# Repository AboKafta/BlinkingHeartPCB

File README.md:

# BlinkingHeartPCB
## Initial Prototype (Summer 2025)

A simple prototype was first made during the summer of 2025 as a gift for my girlfriend. After looking up some tutorials and many hours, I got a simple prototype. I tumbled into some problems such as putting footprints, design errors, and generating a BoM. After using JLCPCB, this is how it was supposed to look. However, after seeing how much it would cost and if it would even work, I didn't continue to manufacture it. A lot of steps were missed in the process (correct factory specifications, wrong gerber file, etc…) and contained a variety of through-hole and SMD parts.

## Second Iteration (2026)

The goal is to make around the same but this time using a 555 timer to make it blink, use only through-hole components to make it easily solderable, and make it smaller and more appeasing. 

# Prototype

Using a guide from https://www.instructables.com/Flashing-LED-using-555-Timer/, a prototype on TinkerCAD was built. Modifications were:

- potentiometer which acts as a rheostat to change blinking speed instead of 1 set blinking speed
- 13 additional LEDs with 100ohm corresponding resistor
- 9V battery to 3V battery cell for convenience, with switch added

A prototype was made in TinkerCAD to check if everything works well before going on to making a schematic: https://www.tinkercad.com/things/8CvfxhTKkNE-blinking-led

# Schematic

Helpful KiCad tutorial: https://www.youtube.com/watch v=HAlTS3Bm8C4&list=PLUOaI24LpvQPls1Ru_qECJrENwzD7XImd&index=3

In KiCad, the base schematic was transformed from:

To:

Notes:

- Resistor values on LEDs can be made higher to change duration of cell battery but LEDs won’t be as bright.
- If LED colors wants to be swapped, make sure the forward voltage is around 2V. Anything above 3V will ensure dim lights and low battery run time.
- The battery cell itself was bought off amazon rather than Digikey.
- 50ohm resistors to LEDs were kept to keep the current at a safe level and not rely on the cell battery’s internal resistance which is prone to spikes.
- Make sure the chosen 555 timer takes 3V, some take 4.5V and above only.

Parts Selected:

All items were found off Digikey and contain all the necessary symbols and footprints except the yellow LEDs, but that can be assigned to a basic 5mm LED footprint found on KiCad:

- Switch: https://www.digikey.com/en/products/detail/e-switch/100SP1T1B4M2QE/378824
- 555 Timer: https://www.digikey.com/en/products/detail/renesas-electronics-corporation/ICM7555IPAZ/821488
- 1k Ohm Resistor: https://www.digikey.com/en/products/detail/stackpole-electronics-inc/CF14JT1K00/1741314
- 1 uF Capacitor: https://www.digikey.com/en/products/detail/tdk/FG28X7R1E105KRT06/5803197
- Yellow LEDs: https://www.digikey.com/en/products/detail/kingbright/WP7113SYC/1747679
- 50ohm Resistors: https://www.digikey.com/en/products/detail/yageo/MFR25SFBE52-50R/9142201
- 1Mohm Potentiometer: https://www.digikey.com/en/products/detail/bourns-inc/PDB12-H4301-105BF/3780665

After that, run DRC. If no errors put up, it is safe to continue. Make sure to put limitations of PCB making factory that is chosen before continuing to PCB layout.

# PCB Layout

To get heart-shape, use the basic tools given. Make 2 semi-circles and have their 2 parallel lines from the endpoints intersect. After that, I updated PCB from schematic and laid out all the components. I placed the resistors and LCDs next to the each other so vias weren’t necessary for my case. After that, I refilled and rechecked the DRC, giving 0 warnings and error. I then added some finishing touches with the silk layer. Below are all the pictures:

Total Costs —> 46$ ($13 for PCB, $33 for parts)

# Soldering:

Below are results of the outcome. The LEDs were working while soldering, but stopped working. At first, I thought the LEDs were taking too much amps so I removed some LEDs, but it still wasn’t working. I put my multimeter to measure amps and the lights were lighting up when I was testing leads. However, 2 lights weren’t lighting up. This was because their legs were touching together. After fixing that, all the lights started lighting up and it was all working.

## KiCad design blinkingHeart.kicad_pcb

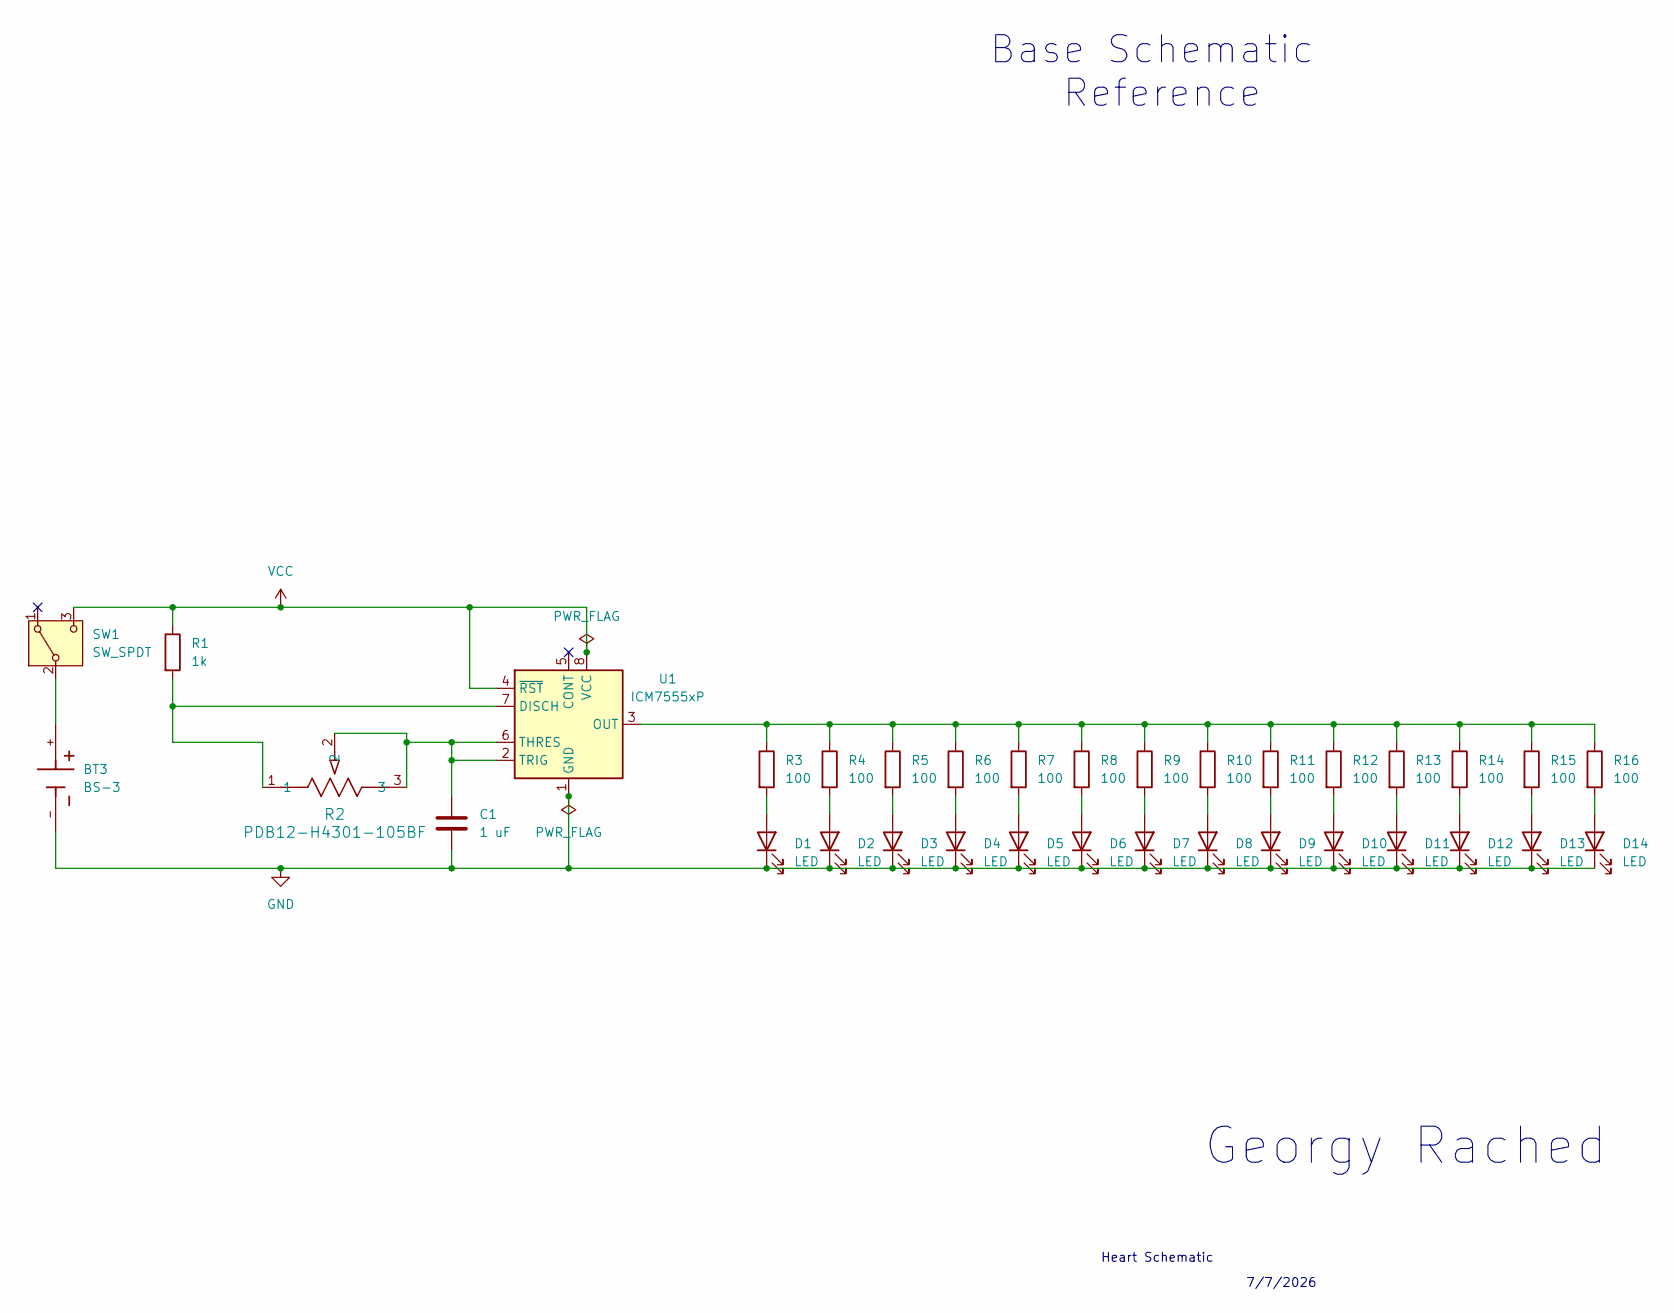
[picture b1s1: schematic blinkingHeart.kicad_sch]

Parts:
BT3: BS-3; BAT_BS-3; PARTREV F
C1: 1 uF; CAP_FG28_TDK
D1, D2, D3, D4, D5, D6, D7, D8, D9, D10, D11, D12, D13, D14: LED; LED_D5.0mm_Clear
R1: 1k; STA_CF14_STP
R2: PDB12-H4301-105BF; POT_PDB12-H_301_BRN
R3, R4, R5, R6, R7, R8, R9, R10, R11, R12, R13, R14, R15, R16: 100; RESAD730W45L370D210
SW1: SW_SPDT; SW_100SP1T1B4M2QE
U1: ICM7555xP; DIP254P762X533-8

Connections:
GND: BT3.-, C1.2, D1.1 (K), D2.1 (K), D3.1 (K), D4.1 (K), D5.1 (K), D6.1 (K), D7.1 (K), D8.1 (K), D9.1 (K), D10.1 (K), D11.1 (K), D12.1 (K), D13.1 (K), D14.1 (K), U1.1 (GND)
unnamed: D1.2 (A), R3.2
unnamed: D2.2 (A), R4.2
unnamed: D3.2 (A), R5.2
unnamed: D4.2 (A), R6.2
unnamed: D5.2 (A), R7.2
unnamed: D6.2 (A), R8.2
unnamed: D7.2 (A), R9.2
unnamed: D8.2 (A), R10.2
unnamed: D9.2 (A), R11.2
unnamed: D10.2 (A), R12.2
unnamed: D11.2 (A), R13.2
unnamed: D12.2 (A), R14.2
unnamed: D13.2 (A), R15.2
unnamed: D14.2 (A), R16.2
unnamed: BT3.+, SW1.2 (B)
unnamed: R1.2, R2.1, U1.7 (DISCH)
unnamed: R3.1, R4.1, R5.1, R6.1, R7.1, R8.1, R9.1, R10.1, R11.1, R12.1, R13.1, R14.1, R15.1, R16.1, U1.3 (OUT)
unnamed: C1.1, R2.2, R2.3, U1.2 (TRIG), U1.6 (THRES)
VCC: R1.1, SW1.3 (C), U1.4 (~RST), U1.8 (VCC)

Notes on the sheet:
Base Schematic Reference
Heart Schematic
7/7/2026
Georgy Rached

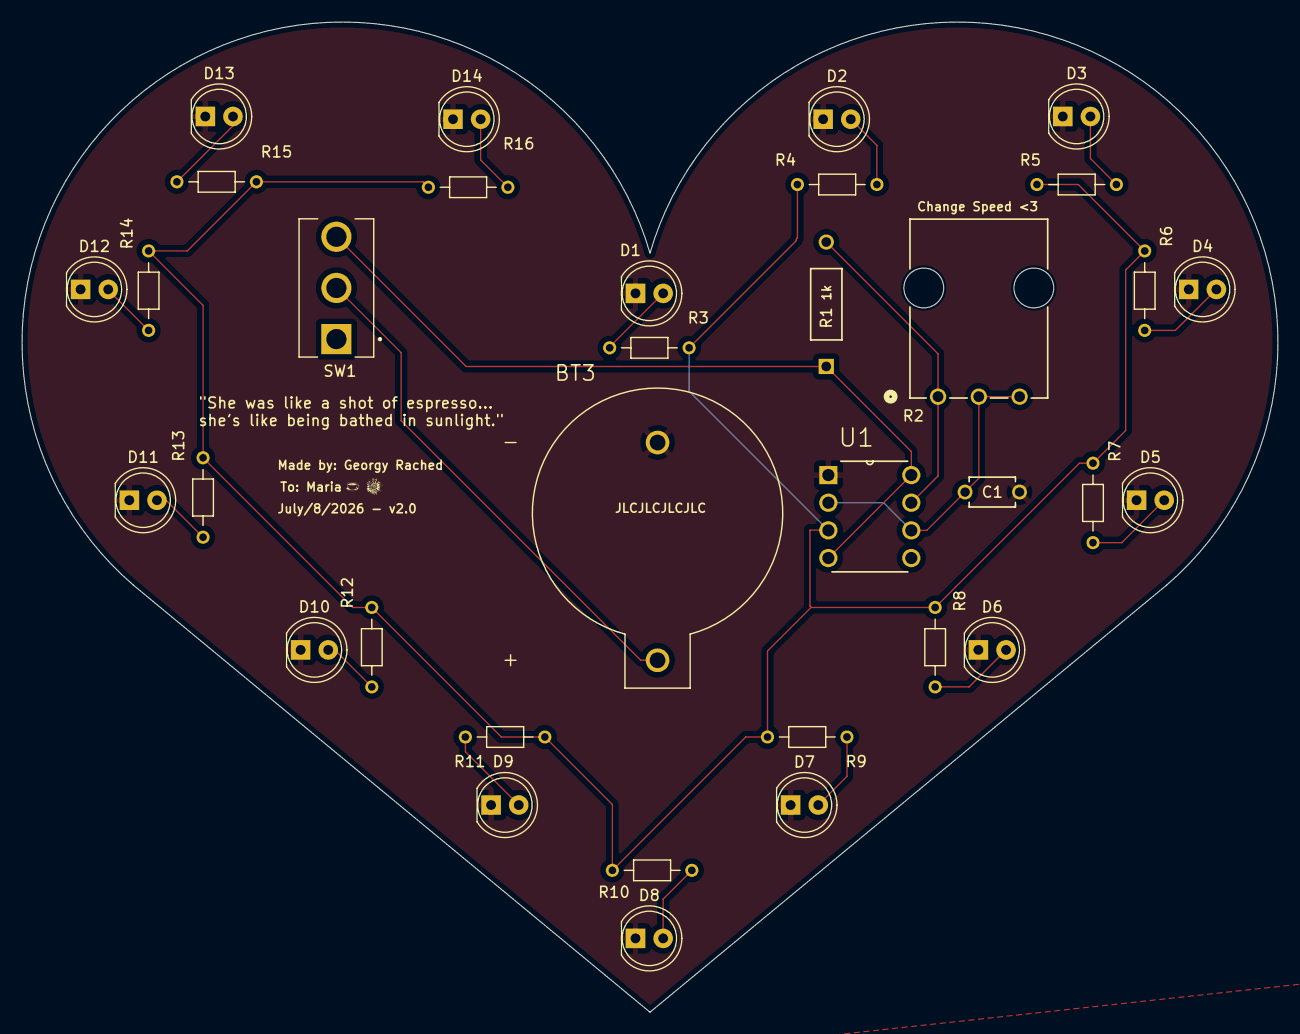
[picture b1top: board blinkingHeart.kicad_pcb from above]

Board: 2 copper layers, 115.4 x 90.9 mm, 34 parts (0 on the bottom side), 20 nets.
